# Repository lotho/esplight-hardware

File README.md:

# esplight-hardware
Board to control a WS2812B stripe with an ESP8266

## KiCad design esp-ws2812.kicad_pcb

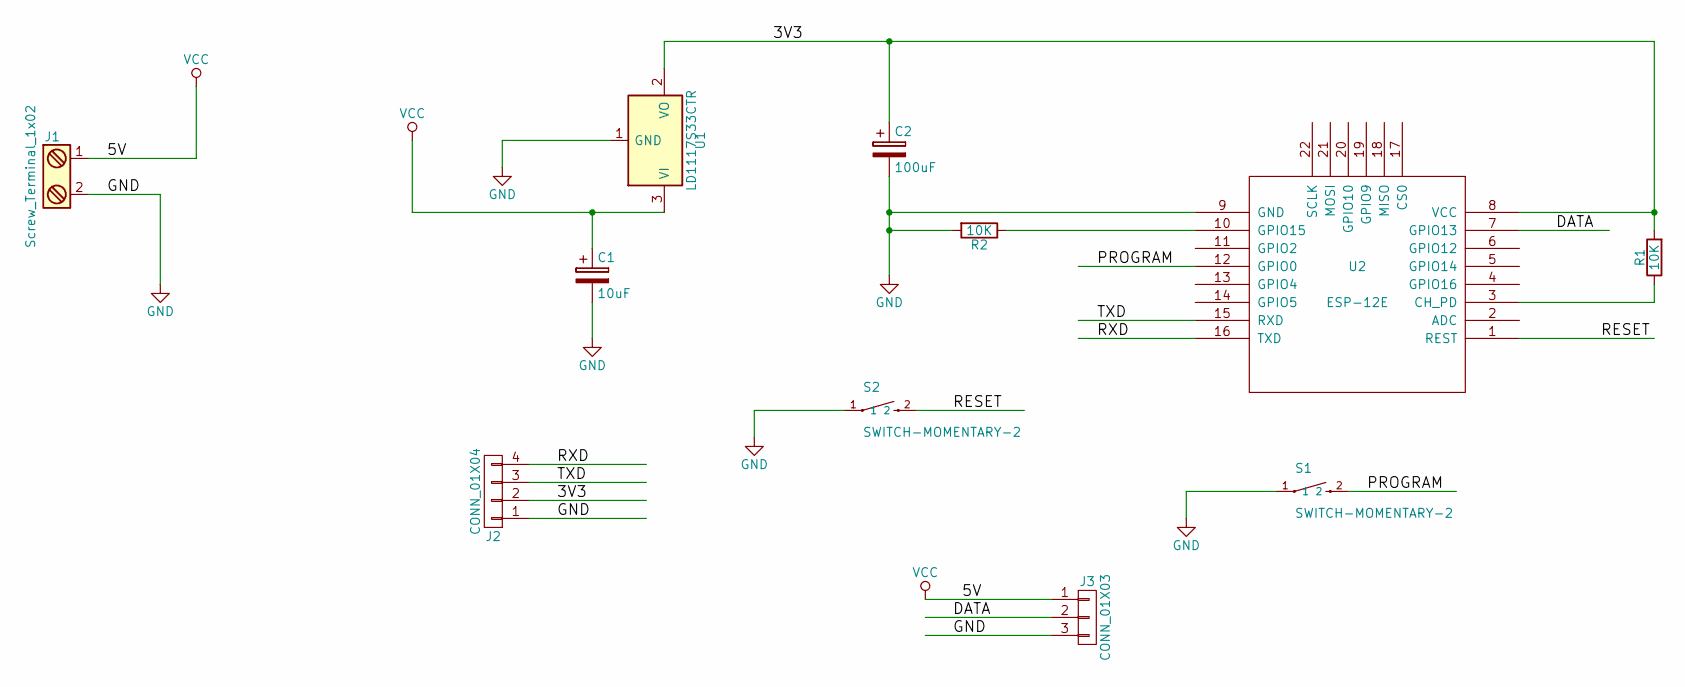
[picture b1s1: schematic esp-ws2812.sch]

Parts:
C1: 10uF; CP_Radial_Tantal_D4.5mm_P2.50mm
C2: 100uF; CP_Radial_Tantal_D4.5mm_P2.50mm
J1: Screw_Terminal_1x02; SCREWTERMINAL-5MM-2
J2: CONN_01X04; Pin_Header_Straight_1x04_Pitch2.54mm
J3: CONN_01X03; Pin_Header_Straight_1x03_Pitch2.54mm
R1, R2: 10K; R_Axial_DIN0207_L6.3mm_D2.5mm_P10.16mm_Horizontal
S1, S2: SWITCH-MOMENTARY-2; SW_PUSH_6mm
U1: LD1117S33CTR; SOT-223
U2: ESP-12E

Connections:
/3V3: C2.1, J2.2, R1.2, U1.2 (VO), U2.8 (VCC)
/DATA: J3.2, U2.7 (GPIO13)
/PROGRAM: S1.2, U2.12 (GPIO0)
/RESET: S2.2, U2.1 (REST)
/RXD: J2.4, U2.16 (TXD)
/TXD: J2.3, U2.15 (RXD)
GND: C1.2, C2.2, J1.2, J2.1, J3.3, R2.2, S1.1, S2.1, U1.1 (GND), U2.9 (GND)
unnamed: R1.1, U2.3 (CH_PD)
unnamed: R2.1, U2.10 (GPIO15)
VCC: C1.1, J1.1, J3.1, U1.3 (VI)

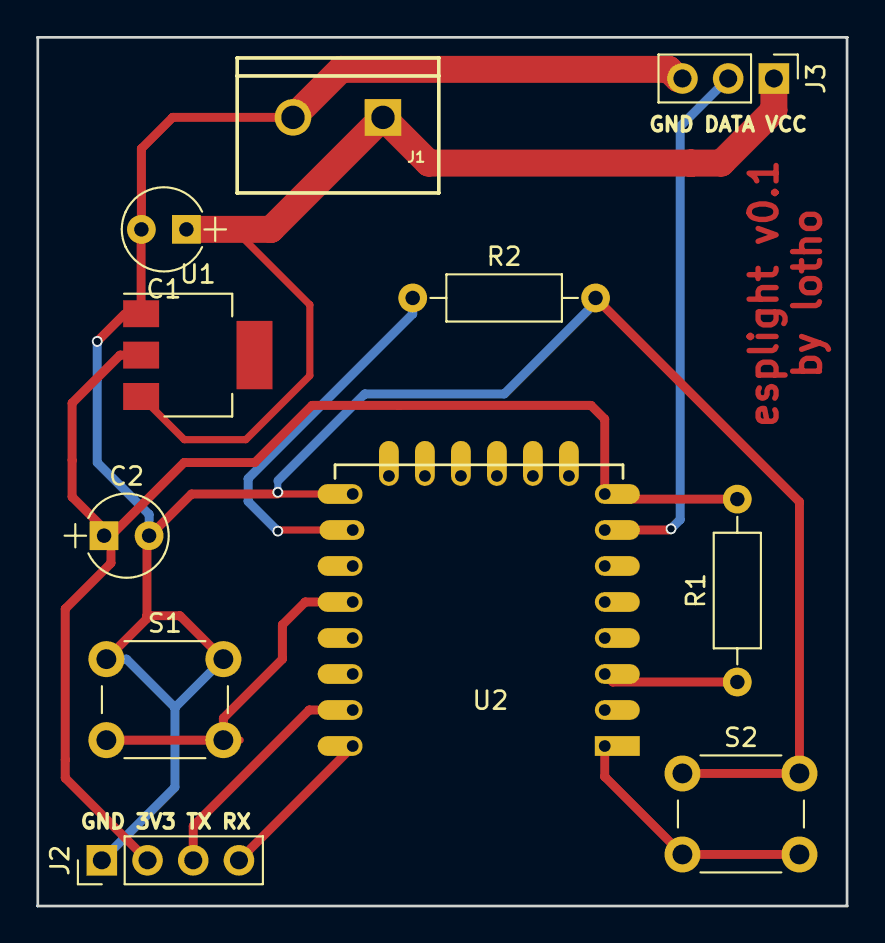
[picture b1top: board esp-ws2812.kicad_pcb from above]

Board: 2 copper layers, 45.0 x 48.3 mm, 11 parts (0 on the bottom side), 10 nets.

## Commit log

2018-06-30 added the kicad files
